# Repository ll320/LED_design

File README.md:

# LED Acrylic Sheet Display
* Great for home or office display, and can be used as a good looking night light. Customize your own LED color and acrylic sheet design!
* Fit for children of ages 6+ with guidance of an adult. PCB is visible to the user, and can be an accessable way to learn about how electronics work. If you are interested, you may even make your own program for the light with the Atmega chip (Arduino board and original code provided)!
* It can also survive 3 foot drop with battery installed~

# Usage Notes

## Variable Light Intensity
* LED light is button-activated to switch between the following operating modes:
  1. `Off`
  1. `Brightest`
  1. `Intermediate Brightness`
  1. `Least Bright`
  1. `Flashing @ 2 Hz`

## Components Included
* single battery of 9 V:
    + easily replacable
    + battery life - (assuming 500mAh capacity) **16 hrs** on brightest mode, **26 hrs** on least bright mode, **32 hrs** off
* single-sided PCB (printed circuit board)
    + Atmega chip removable for reprogramming
    + LED changable
* 5 LEDs: red, blue, green, yellow, white
* 3 acrylic designs
* lid
* box

## Dimensions
* Box -- h:25mm x w:55mm x l:124mm
* Acrylic sheet -- 3mm x 110mm x 110mm

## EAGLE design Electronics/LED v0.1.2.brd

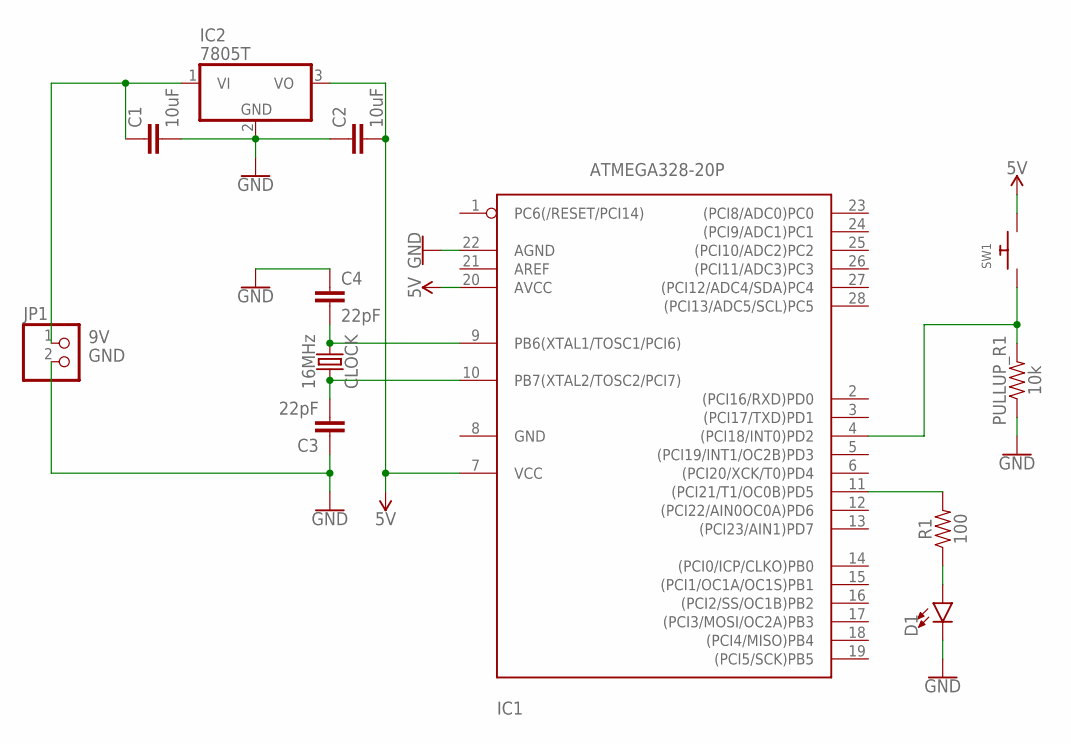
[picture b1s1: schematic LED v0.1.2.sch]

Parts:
C1, C2: 10uF; 1210
C3, C4: 22pF; 0603
CLOCK: 16MHz; HC49US
D1: LED5MM; LED_5MM
IC1: ATMEGA328-20P; DIL28-3
IC2: 7805T; TO220H
JP1: PINHD-1X2; 1X02
PULLUP_R1: 10k; AXIAL-0.3
R1: 100; AXIAL-0.3
SW1: SWITCH_PUSHBUTTONEVQ-PE; TACT_PANA-EVQ

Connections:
5V: C2.2, IC1.7 (VCC), IC1.20 (AVCC), IC2.3 (VO), SW1.P$2
9V: C1.1, IC2.1 (VI), JP1.1
GND: C1.2, C2.1, C3.1, C4.1, D1.K (C), IC1.22 (AGND), IC2.2 (GND), JP1.2, PULLUP_R1.P$1 (1)
unnamed: IC1.4 ((PCI18/INT0)PD2), PULLUP_R1.P$2 (2), SW1.P$1
unnamed: IC1.11 ((PCI21/T1/OC0B)PD5), R1.P$2 (2)
unnamed: C4.2, CLOCK.1, IC1.9 (PB6(XTAL1/TOSC1/PCI6))
unnamed: C3.2, CLOCK.2, IC1.10 (PB7(XTAL2/TOSC2/PCI7))
unnamed: D1.A, R1.P$1 (1)

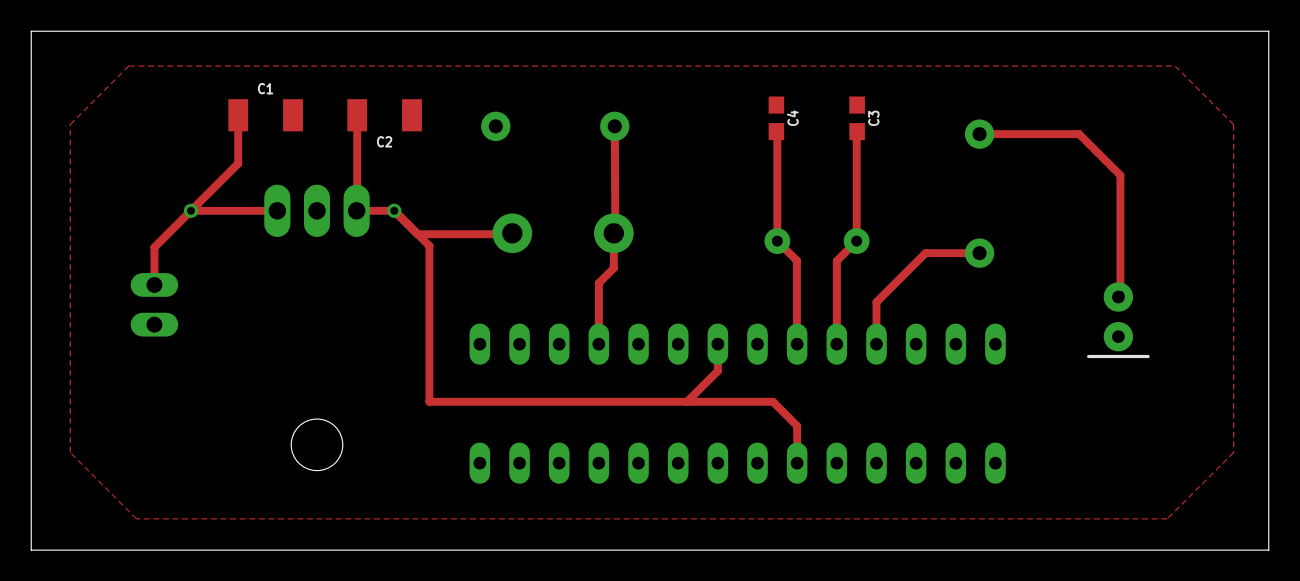
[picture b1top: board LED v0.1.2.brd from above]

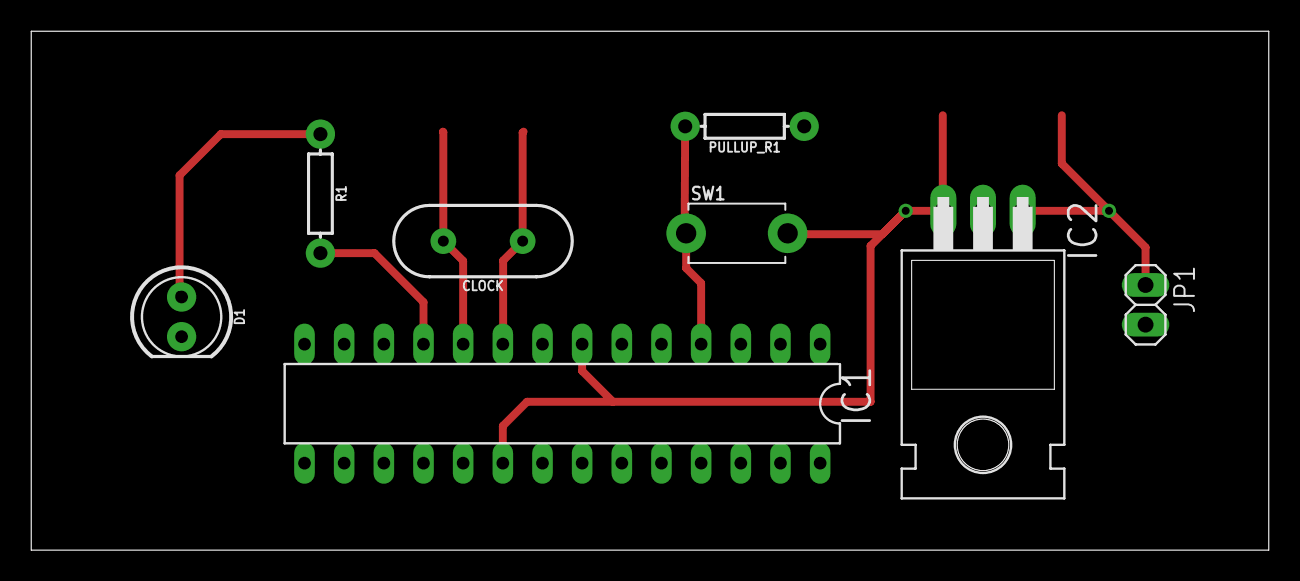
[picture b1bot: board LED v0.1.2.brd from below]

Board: 2 copper layers, 79.2 x 33.2 mm, 12 parts (8 on the bottom side), 8 nets.

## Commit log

2018-11-01 Create Electronics
2018-11-01 Create Mechanical
2018-11-01 Create Software
2018-11-01 Create Testing
2018-11-01 Create Docs
2018-11-01 Create ll
2018-11-01 Create file
2018-12-13 Rename LED_wchip.brd to LED_v0.1.1.brd
2018-12-13 Rename LED_wchip.sch to LED_v.0.1.1.sch
2018-12-13 Add files via upload
    Previous pin 11 changed to pin 5 (Arduino pin11 is atmega chip pin5)
2018-12-13 Rename LED_v.0.1.1.sch to LED v.0.1.1.sch
2018-12-13 Rename LED_v0.1.1.brd to LED v0.1.1.brd
2018-12-13 Changed input from pin2 to pin4
    Atmega chip pin4 is Arduino pin2
2018-12-13 changed output pin11 to pin5
2018-12-16 Rename LED v.0.1.1.sch to LED v0.1.1.sch
2018-12-16 Update file
2018-12-16 Rename file to Design Guideline
2018-12-16 Create Improvements that can be made

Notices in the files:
parts and their libraries:
SparkFun-Capacitors: Licensing: Creative Commons ShareAlike 4.0 International - https://creativecommons.org/licenses/by-sa/4.0
